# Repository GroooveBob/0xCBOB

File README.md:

# 0xCBOB
ortho board in static style

[the wonderful dreipunkteinsvier made the QMK Firmware](https://github.com/dreipunkteinsvier/qmk-config-0xCBOB)

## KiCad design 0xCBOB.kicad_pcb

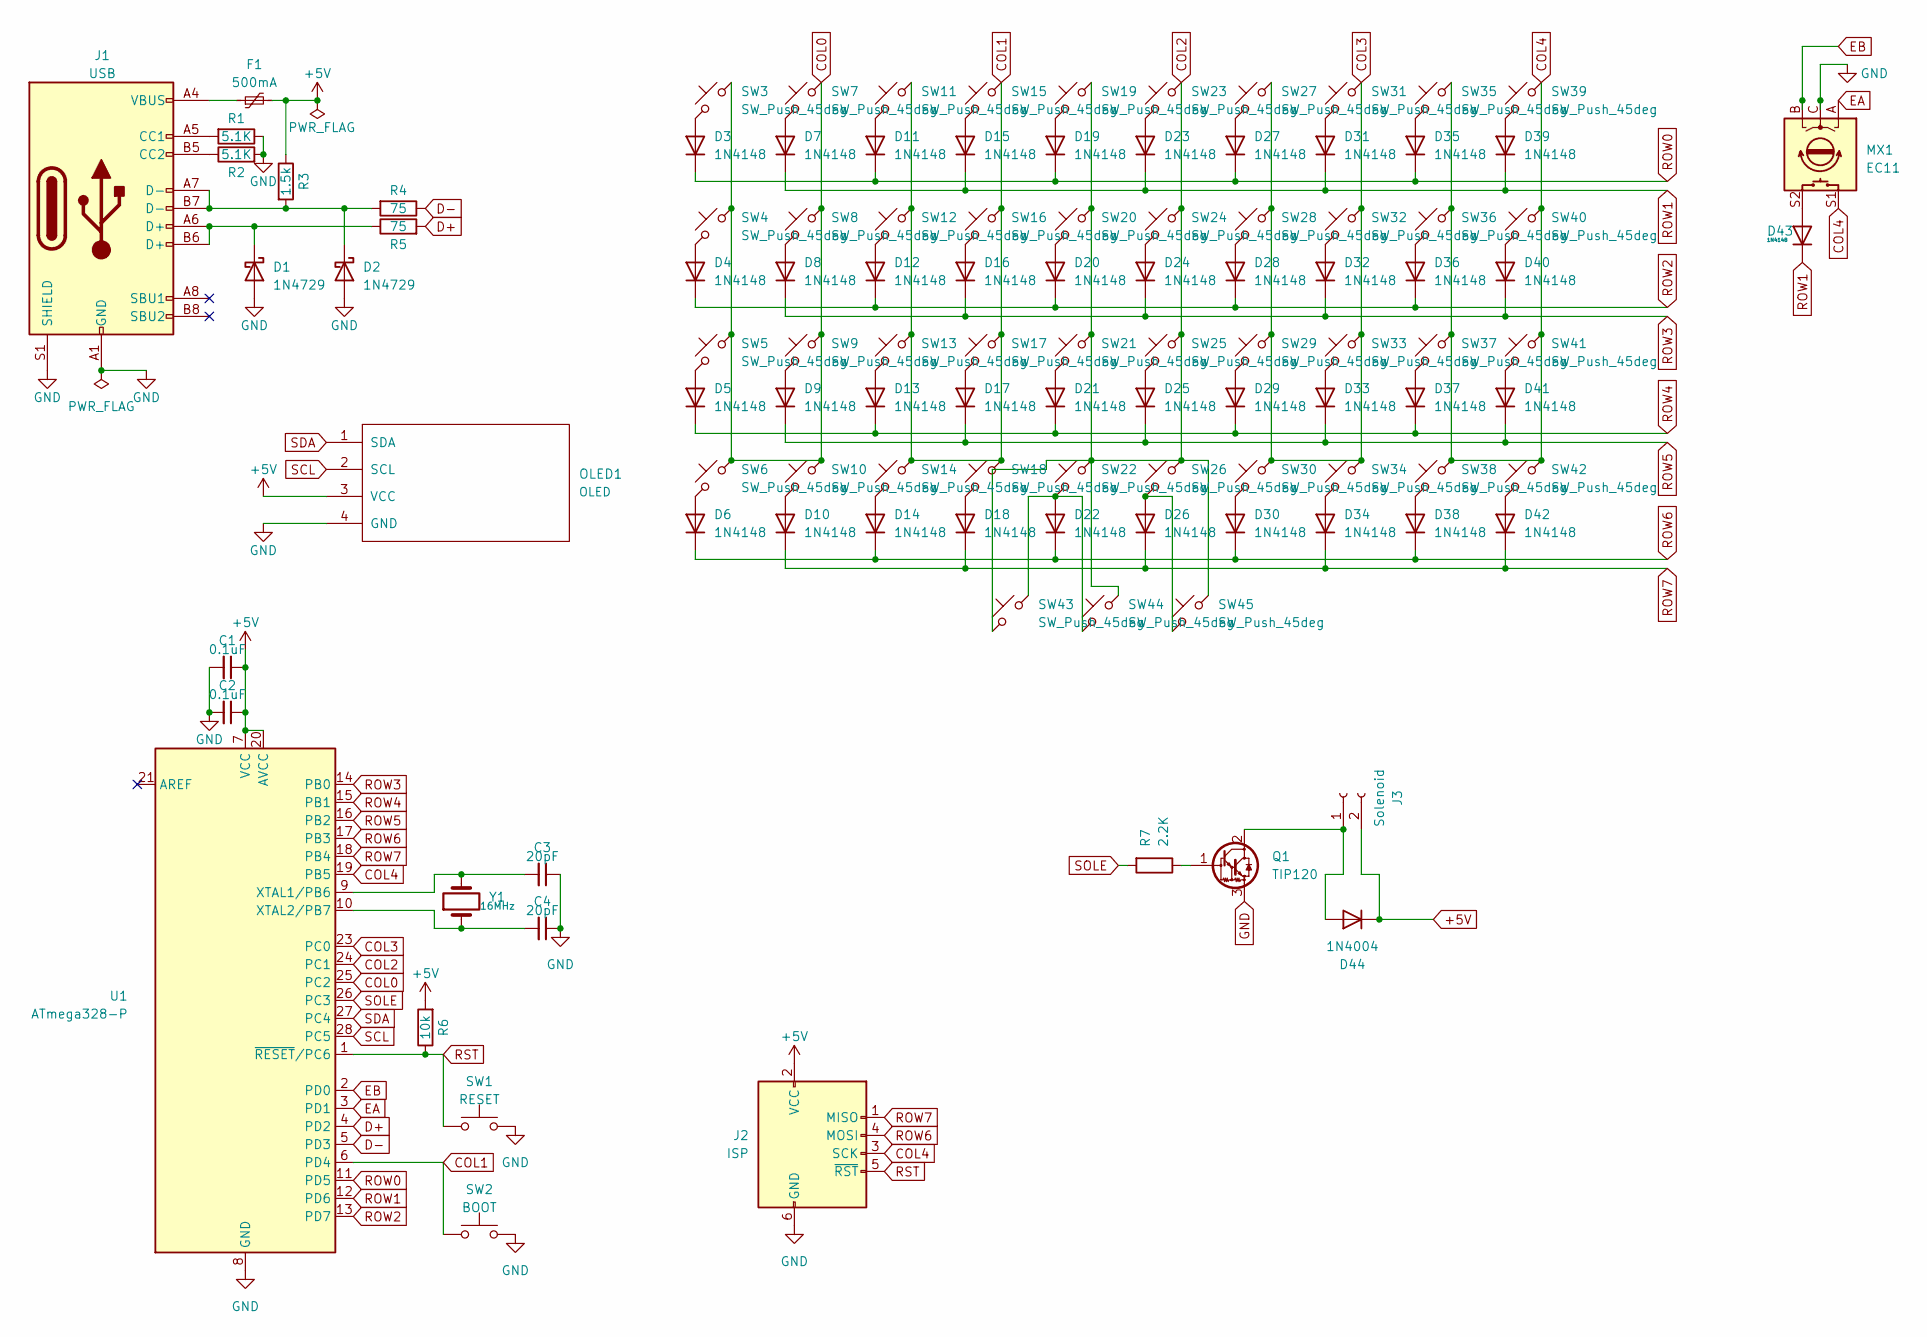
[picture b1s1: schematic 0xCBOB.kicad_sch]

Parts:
C1, C2: 0.1uF; C_Disc_D5.0mm_W2.5mm_P5.00mm; Part Nb. C277965
C3, C4: 20pF; C_Disc_D3.0mm_W1.6mm_P2.50mm; Part Nb. C254096
D1, D2: 1N4729; D_DO-41_SOD81_P7.62mm_Horizontal; Part Nb. C2532
D3, D4, D5, D6, D7, D8, D9, D10, D11, D12, D13, D14, D15, D16, D17, D18, D19, D20, D21, D22, D23, D24, D25, D26, D27, D28, D29, D30, D31, D32, D33, D34, D35, D36, D37, D38, D39, D40, D41, D42: 1N4148; D_DO-35_SOD27_P7.62mm_Horizontal
D43: 1N4148; D_DO-35_SOD27_P7.62mm_Horizontal; Part Nb. C14538
D44: 1N4004; D_DO-41_SOD81_P10.16mm_Horizontal
F1: 500mA; Fuse_BelFuse_0ZRE0025FF_L9.6mm_W3.8mm; Part Nb. C268799
J1: USB; USB_C_Receptacle_GCT_USB4085; Part Nb. 2073-USB4085-GF-ACT-ND
J2: ISP; PinHeader_2x03_P2.54mm_Vertical
J3: Solenoid; JST_EH_S2B-EH_1x02_P2.50mm_Horizontal
MX1: EC11; RotaryEncoder_Alps_EC11E-Switch_Vertical_H20mm; Part Nb. amz
OLED1: OLED; PinSocket_1x04_P2.54mm_Vertical; Part Nb. amz
Q1: TIP120; TO-220-3_Horizontal_TabDown
R1, R2: 5.1K; R_Axial_DIN0204_L3.6mm_D1.6mm_P5.08mm_Horizontal; Part Nb. C58676
R3: 1.5k; R_Axial_DIN0204_L3.6mm_D1.6mm_P5.08mm_Horizontal; Part Nb. C433494
R4, R5: 75; R_Axial_DIN0204_L3.6mm_D1.6mm_P5.08mm_Horizontal; Part Nb. C713897
R6: 10k; R_Axial_DIN0204_L3.6mm_D1.6mm_P5.08mm_Horizontal; Part Nb. C58673
R7: 2.2K; R_Axial_DIN0204_L3.6mm_D1.6mm_P5.08mm_Horizontal
SW1: RESET; SW_PUSH_6mm_H5mm; Part Nb. C127509
SW2: BOOT; SW_PUSH_6mm_H5mm; Part Nb. C127509
SW3, SW4, SW5, SW6, SW7, SW8, SW9, SW10, SW11, SW12, SW13, SW14, SW15, SW16, SW17, SW18, SW19, SW20, SW21, SW22, SW23, SW24, SW25, SW26, SW27, SW28, SW29, SW30, SW31, SW32, SW33, SW34, SW35, SW36, SW37, SW38, SW39, SW40, SW41, SW42: SW_Push_45deg; SW_Cherry_MX_1.00u_PCB
SW43, SW44, SW45: SW_Push_45deg; MXOnly-2U-ReversedStabilizers-NoLED
U1: ATmega328-P; DIP-28_W7.62mm; Part Nb. C613508
Y1: 16MHz; Crystal_HC49-4H_Vertical; Part Nb. C16212

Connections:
+5V: C1.1, C2.1, D44.1 (K), F1.2, J2.2 (VCC), J3.2, OLED1.3 (VCC), R3.1, R6.2, U1.7 (VCC), U1.20 (AVCC)
COL0: SW3.2, SW4.2, SW5.2, SW6.2, SW7.2, SW8.2, SW9.2, SW10.2, U1.25 (PC2)
COL1: SW2.1, SW11.2, SW12.2, SW13.2, SW14.2, SW15.2, SW16.2, SW17.2, SW18.2, U1.6 (PD4)
COL2: SW19.2, SW20.2, SW21.2, SW22.2, SW23.2, SW24.2, SW25.2, SW26.2, SW43.1, SW44.2, SW45.2, U1.24 (PC1)
COL3: SW27.2, SW28.2, SW29.2, SW30.2, SW31.2, SW32.2, SW33.2, SW34.2, U1.23 (PC0)
COL4: J2.3 (SCK), MX1.S1, SW35.2, SW36.2, SW37.2, SW38.2, SW39.2, SW40.2, SW41.2, SW42.2, U1.19 (PB5)
D+: R5.2, U1.4 (PD2)
D-: R4.1, U1.5 (PD3)
EA: MX1.A, U1.3 (PD1)
EB: MX1.B, U1.2 (PD0)
GND: C1.2, C2.2, C3.1, C4.1, D1.2 (A), D2.2 (A), J1.A1 (GND), J1.A12 (GND), J1.B1 (GND), J1.B12 (GND), J1.S1 (SHIELD), J2.6 (GND), MX1.C, OLED1.4 (GND), Q1.3 (E), R1.1, R2.2, SW1.2, SW2.2, U1.8 (GND), U1.22 (GND)
unnamed: C3.2, U1.9 (XTAL1/PB6), Y1.2
unnamed: C4.2, U1.10 (XTAL2/PB7), Y1.1
unnamed: D1.1 (K), J1.A6 (D+), J1.B6 (D+), R5.1
unnamed: D2.1 (K), J1.A7 (D-), J1.B7 (D-), R3.2, R4.2
unnamed: D3.2 (A), SW3.1
unnamed: D4.2 (A), SW4.1
unnamed: D5.2 (A), SW5.1
unnamed: D6.2 (A), SW6.1
unnamed: D7.2 (A), SW7.1
unnamed: D8.2 (A), SW8.1
unnamed: D9.2 (A), SW9.1
unnamed: D10.2 (A), SW10.1
unnamed: D11.2 (A), SW11.1
unnamed: D12.2 (A), SW12.1
unnamed: D13.2 (A), SW13.1
unnamed: D14.2 (A), SW14.1
unnamed: D15.2 (A), SW15.1
unnamed: D16.2 (A), SW16.1
unnamed: D17.2 (A), SW17.1
unnamed: D18.2 (A), SW18.1
unnamed: D19.2 (A), SW19.1
unnamed: D20.2 (A), SW20.1
unnamed: D21.2 (A), SW21.1
unnamed: D22.2 (A), SW22.1, SW43.2, SW44.1
unnamed: D23.2 (A), SW23.1
unnamed: D24.2 (A), SW24.1
unnamed: D25.2 (A), SW25.1
unnamed: D26.2 (A), SW26.1, SW45.1
unnamed: D27.2 (A), SW27.1
unnamed: D28.2 (A), SW28.1
unnamed: D29.2 (A), SW29.1
unnamed: D30.2 (A), SW30.1
unnamed: D31.2 (A), SW31.1
unnamed: D32.2 (A), SW32.1
unnamed: D33.2 (A), SW33.1
unnamed: D34.2 (A), SW34.1
unnamed: D35.2 (A), SW35.1
unnamed: D36.2 (A), SW36.1
unnamed: D37.2 (A), SW37.1
unnamed: D38.2 (A), SW38.1
unnamed: D39.2 (A), SW39.1
unnamed: D40.2 (A), SW40.1
unnamed: D41.2 (A), SW41.1
unnamed: D42.2 (A), SW42.1
unnamed: D43.2 (A), MX1.S2
unnamed: D44.2 (A), J3.1, Q1.2 (C)
unnamed: F1.1, J1.A4 (VBUS), J1.A9 (VBUS), J1.B4 (VBUS), J1.B9 (VBUS)
unnamed: J1.A5 (CC1), R1.2
unnamed: J1.B5 (CC2), R2.1
unnamed: Q1.1 (B), R7.1
ROW0: D3.1 (K), D11.1 (K), D19.1 (K), D27.1 (K), D35.1 (K), U1.11 (PD5)
ROW1: D7.1 (K), D15.1 (K), D23.1 (K), D31.1 (K), D39.1 (K), D43.1 (K), U1.12 (PD6)
ROW2: D4.1 (K), D12.1 (K), D20.1 (K), D28.1 (K), D36.1 (K), U1.13 (PD7)
ROW3: D8.1 (K), D16.1 (K), D24.1 (K), D32.1 (K), D40.1 (K), U1.14 (PB0)
ROW4: D5.1 (K), D13.1 (K), D21.1 (K), D29.1 (K), D37.1 (K), U1.15 (PB1)
ROW5: D9.1 (K), D17.1 (K), D25.1 (K), D33.1 (K), D41.1 (K), U1.16 (PB2)
ROW6: D6.1 (K), D14.1 (K), D22.1 (K), D30.1 (K), D38.1 (K), J2.4 (MOSI), U1.17 (PB3)
ROW7: D10.1 (K), D18.1 (K), D26.1 (K), D34.1 (K), D42.1 (K), J2.1 (MISO), U1.18 (PB4)
RST: J2.5 (~RST), R6.1, SW1.1, U1.1 (~RESET/PC6)
SCL: OLED1.2 (SCL), U1.28 (PC5)
SDA: OLED1.1 (SDA), U1.27 (PC4)
SOLE: R7.2, U1.26 (PC3)

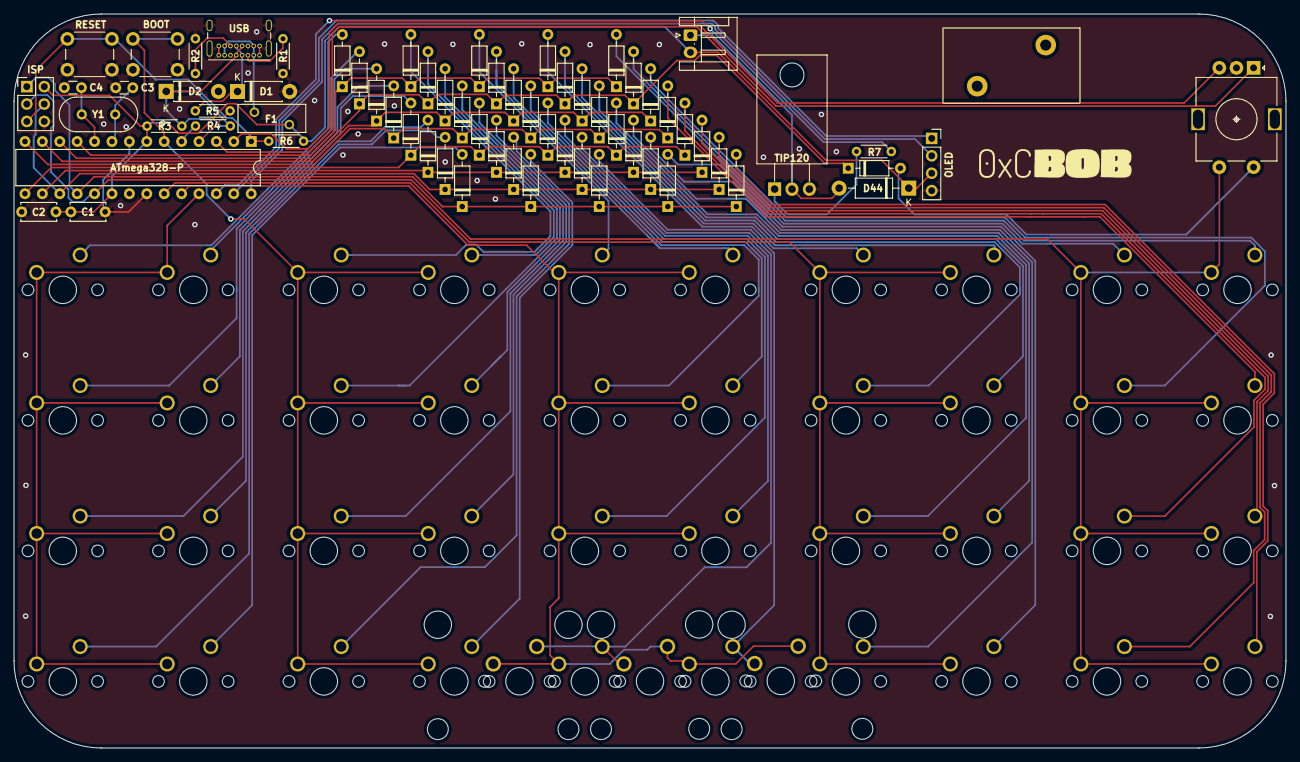
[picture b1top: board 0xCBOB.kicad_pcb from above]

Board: 2 copper layers, 185.6 x 107.1 mm, 109 parts (0 on the bottom side), 73 nets.

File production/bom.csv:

Designator,Footprint,Quantity,Value,LCSC Part #
SW40,SW_Cherry_MX_1.00u_PCB,1,SW_Push_45deg,
D9,D_DO-35_SOD27_P7.62mm_Horizontal,1,1N4148,
SW24,SW_Cherry_MX_1.00u_PCB,1,SW_Push_45deg,
D34,D_DO-35_SOD27_P7.62mm_Horizontal,1,1N4148,
SW9,SW_Cherry_MX_1.00u_PCB,1,SW_Push_45deg,
SW15,SW_Cherry_MX_1.00u_PCB,1,SW_Push_45deg,
SW45,MXOnly-2U-ReversedStabilizers-NoLED,1,SW_Push_45deg,
D40,D_DO-35_SOD27_P7.62mm_Horizontal,1,1N4148,
D10,D_DO-35_SOD27_P7.62mm_Horizontal,1,1N4148,
D26,D_DO-35_SOD27_P7.62mm_Horizontal,1,1N4148,
J1,USB_C_Receptacle_GCT_USB4085,1,USB,
C3,C_Disc_D3.0mm_W1.6mm_P2.50mm,1,20pF,
SW32,SW_Cherry_MX_1.00u_PCB,1,SW_Push_45deg,
OLED1,PinSocket_1x04_P2.54mm_Vertical,1,OLED,
D8,D_DO-35_SOD27_P7.62mm_Horizontal,1,1N4148,
D32,D_DO-35_SOD27_P7.62mm_Horizontal,1,1N4148,
D33,D_DO-35_SOD27_P7.62mm_Horizontal,1,1N4148,
R5,R_Axial_DIN0204_L3.6mm_D1.6mm_P5.08mm_Horizontal,1,75,
SW18,SW_Cherry_MX_1.00u_PCB,1,SW_Push_45deg,
R7,R_Axial_DIN0204_L3.6mm_D1.6mm_P5.08mm_Horizontal,1,2.2K,
Y1,Crystal_HC49-4H_Vertical,1,16MHz,
SW27,SW_Cherry_MX_1.00u_PCB,1,SW_Push_45deg,
SW34,SW_Cherry_MX_1.00u_PCB,1,SW_Push_45deg,
D37,D_DO-35_SOD27_P7.62mm_Horizontal,1,1N4148,
SW31,SW_Cherry_MX_1.00u_PCB,1,SW_Push_45deg,
D42,D_DO-35_SOD27_P7.62mm_Horizontal,1,1N4148,
SW12,SW_Cherry_MX_1.00u_PCB,1,SW_Push_45deg,
SW43,MXOnly-2U-ReversedStabilizers-NoLED,1,SW_Push_45deg,
D20,D_DO-35_SOD27_P7.62mm_Horizontal,1,1N4148,
SW16,SW_Cherry_MX_1.00u_PCB,1,SW_Push_45deg,
SW38,SW_Cherry_MX_1.00u_PCB,1,SW_Push_45deg,
D11,D_DO-35_SOD27_P7.62mm_Horizontal,1,1N4148,
D31,D_DO-35_SOD27_P7.62mm_Horizontal,1,1N4148,
D2,D_DO-41_SOD81_P7.62mm_Horizontal,1,1N4729,
U1,DIP-28_W7.62mm,1,ATmega328-P,
SW21,SW_Cherry_MX_1.00u_PCB,1,SW_Push_45deg,
SW3,SW_Cherry_MX_1.00u_PCB,1,SW_Push_45deg,
D18,D_DO-35_SOD27_P7.62mm_Horizontal,1,1N4148,
F1,Fuse_BelFuse_0ZRE0025FF_L9.6mm_W3.8mm,1,500mA,
D21,D_DO-35_SOD27_P7.62mm_Horizontal,1,1N4148,
D35,D_DO-35_SOD27_P7.62mm_Horizontal,1,1N4148,
SW39,SW_Cherry_MX_1.00u_PCB,1,SW_Push_45deg,
SW5,SW_Cherry_MX_1.00u_PCB,1,SW_Push_45deg,
D4,D_DO-35_SOD27_P7.62mm_Horizontal,1,1N4148,
R4,R_Axial_DIN0204_L3.6mm_D1.6mm_P5.08mm_Horizontal,1,75,
D25,D_DO-35_SOD27_P7.62mm_Horizontal,1,1N4148,
SW20,SW_Cherry_MX_1.00u_PCB,1,SW_Push_45deg,
D16,D_DO-35_SOD27_P7.62mm_Horizontal,1,1N4148,
SW19,SW_Cherry_MX_1.00u_PCB,1,SW_Push_45deg,
SW33,SW_Cherry_MX_1.00u_PCB,1,SW_Push_45deg,
SW6,SW_Cherry_MX_1.00u_PCB,1,SW_Push_45deg,
MX1,RotaryEncoder_Alps_EC11E-Switch_Vertical_H20mm,1,EC11,
D7,D_DO-35_SOD27_P7.62mm_Horizontal,1,1N4148,
SW7,SW_Cherry_MX_1.00u_PCB,1,SW_Push_45deg,
SW13,SW_Cherry_MX_1.00u_PCB,1,SW_Push_45deg,
SW41,SW_Cherry_MX_1.00u_PCB,1,SW_Push_45deg,
D44,D_DO-41_SOD81_P10.16mm_Horizontal,1,1N4004,
D12,D_DO-35_SOD27_P7.62mm_Horizontal,1,1N4148,
SW17,SW_Cherry_MX_1.00u_PCB,1,SW_Push_45deg,
D22,D_DO-35_SOD27_P7.62mm_Horizontal,1,1N4148,
SW1,SW_PUSH_6mm_H5mm,1,RESET,
SW37,SW_Cherry_MX_1.00u_PCB,1,SW_Push_45deg,
D5,D_DO-35_SOD27_P7.62mm_Horizontal,1,1N4148,
D19,D_DO-35_SOD27_P7.62mm_Horizontal,1,1N4148,
D27,D_DO-35_SOD27_P7.62mm_Horizontal,1,1N4148,
D6,D_DO-35_SOD27_P7.62mm_Horizontal,1,1N4148,
SW35,SW_Cherry_MX_1.00u_PCB,1,SW_Push_45deg,
C2,C_Disc_D5.0mm_W2.5mm_P5.00mm,1,0.1uF,
R2,R_Axial_DIN0204_L3.6mm_D1.6mm_P5.08mm_Horizontal,1,5.1K,
SW25,SW_Cherry_MX_1.00u_PCB,1,SW_Push_45deg,
Q1,TO-220-3_Horizontal_TabDown,1,TIP120,
SW8,SW_Cherry_MX_1.00u_PCB,1,SW_Push_45deg,
C4,C_Disc_D3.0mm_W1.6mm_P2.50mm,1,20pF,
R1,R_Axial_DIN0204_L3.6mm_D1.6mm_P5.08mm_Horizontal,1,5.1K,
SW26,SW_Cherry_MX_1.00u_PCB,1,SW_Push_45deg,
D17,D_DO-35_SOD27_P7.62mm_Horizontal,1,1N4148,
D13,D_DO-35_SOD27_P7.62mm_Horizontal,1,1N4148,
D14,D_DO-35_SOD27_P7.62mm_Horizontal,1,1N4148,
SW4,SW_Cherry_MX_1.00u_PCB,1,SW_Push_45deg,
D36,D_DO-35_SOD27_P7.62mm_Horizontal,1,1N4148,
J3,JST_EH_S2B-EH_1x02_P2.50mm_Horizontal,1,Solenoid,
SW36,SW_Cherry_MX_1.00u_PCB,1,SW_Push_45deg,
D15,D_DO-35_SOD27_P7.62mm_Horizontal,1,1N4148,
SW29,SW_Cherry_MX_1.00u_PCB,1,SW_Push_45deg,
D24,D_DO-35_SOD27_P7.62mm_Horizontal,1,1N4148,
D28,D_DO-35_SOD27_P7.62mm_Horizontal,1,1N4148,
D39,D_DO-35_SOD27_P7.62mm_Horizontal,1,1N4148,
R3,R_Axial_DIN0204_L3.6mm_D1.6mm_P5.08mm_Horizontal,1,1.5k,
SW30,SW_Cherry_MX_1.00u_PCB,1,SW_Push_45deg,
R6,R_Axial_DIN0204_L3.6mm_D1.6mm_P5.08mm_Horizontal,1,10k,
SW14,SW_Cherry_MX_1.00u_PCB,1,SW_Push_45deg,
D41,D_DO-35_SOD27_P7.62mm_Horizontal,1,1N4148,
D38,D_DO-35_SOD27_P7.62mm_Horizontal,1,1N4148,
SW22,SW_Cherry_MX_1.00u_PCB,1,SW_Push_45deg,
D30,D_DO-35_SOD27_P7.62mm_Horizontal,1,1N4148,
D29,D_DO-35_SOD27_P7.62mm_Horizontal,1,1N4148,
SW10,SW_Cherry_MX_1.00u_PCB,1,SW_Push_45deg,
D43,D_DO-35_SOD27_P7.62mm_Horizontal,1,1N4148,
SW2,SW_PUSH_6mm_H5mm,1,BOOT,
D3,D_DO-35_SOD27_P7.62mm_Horizontal,1,1N4148,
SW42,SW_Cherry_MX_1.00u_PCB,1,SW_Push_45deg,
SW23,SW_Cherry_MX_1.00u_PCB,1,SW_Push_45deg,
SW11,SW_Cherry_MX_1.00u_PCB,1,SW_Push_45deg,
D1,D_DO-41_SOD81_P7.62mm_Horizontal,1,1N4729,
C1,C_Disc_D5.0mm_W2.5mm_P5.00mm,1,0.1uF,
D23,D_DO-35_SOD27_P7.62mm_Horizontal,1,1N4148,
SW44,MXOnly-2U-ReversedStabilizers-NoLED,1,SW_Push_45deg,
SW28,SW_Cherry_MX_1.00u_PCB,1,SW_Push_45deg,

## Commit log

2022-09-29 licence
